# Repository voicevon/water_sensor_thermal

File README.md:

# water_sensor_thermal

污水处理厂三通道脉冲热式管道有液检测传感器（全栈项目：系统设计文档 + KiCad 原理图/PCB + 机械探头工艺 + ESP32 PlatformIO 固件 + 1Hz 串口采数分析工具）。

面向 **碳源、次氯酸钠、聚合氯化铁** 三路强腐蚀/易挂壁/易结垢化工药剂管道（DN75 PPR 水平管），采用 **1 拖 3 单主控盒** 与 **脉冲加热 + 冷却衰减比算法** 实现免标定开箱即用、宽温（-10℃ ~ +60℃）可靠有液/空管检测，支持 **不锈钢/陶瓷探头混合封装**，并通过 **BLE 广播、WiFi Web 后台及 MQTT** 与上位系统（`water_relay` / 监控平台）无缝对接。

---

## 目录结构

```text
water_sensor_thermal/
├── README.md                          # 项目总览与文档索引
├── platformio.ini                     # PlatformIO 构建配置（ESP32 Arduino）
├── src/                               # ESP32 固件源码
│   ├── config.h                       # 硬件引脚、不锈钢/陶瓷算法参数、WiFi/MQTT/BLE 配置
│   ├── main.cpp                       # 1Hz 统一采样、动态分时轮巡调度、串口采数与阶跃测试
│   ├── ThermalChannel.{h,cpp}         # 单通道峰值追踪、冷却衰减比计算、混合封装与迟滞判定
│   ├── ble_adv.{h,cpp}                # 13B BLE 广播封装（兼容 water_sensor_hx711 / water_relay）
│   ├── wifi_mqtt.{h,cpp}              # WiFi 指数退避重连与 MQTT 异步连接/上报/远程控制
│   ├── web_config.{h,cpp}             # AP_STA 配网、Web REST API 与每通道在线配置
│   ├── index_html.h                   # 内嵌紧凑型暗色 SPA 监控与配置页面
│   ├── nvs_config.{h,cpp}             # NVS 掉电持久化（网络、封装类型、阈值、调参基准）
│   └── data_cache.{h,cpp}             # 实时采样数据缓存
├── tools/
│   └── thermal_logger.py              # 1Hz 串口 CSV 采数、阶跃测试与自动绘图分析脚本
├── docs/                              # 完整设计与演进文档
│   ├── design_spec.md                 # 系统设计规格书 (v2.0)：工况、冷却衰减比算法、通信协议
│   ├── main_board_schematic.md        # 主控板原理图与 BOM（最新 DevKit V1 载板版 v4）
│   ├── probe_mechanical_spec.md       # 探头机械结构、标准件清单、混合封装与灌封工艺 (v2.1)
│   ├── hardware_design.md             # 早期裸模组硬件方案草稿与 BOM (v2.0 历史存档)
│   └── pcb_layout.md                  # 早期 PCB 布局规划与布线规范 (v1.0 历史存档)
└── hardware/
    └── pcb/
        ├── main_board_pcb/            # 主控载板 KiCad 工程 (88×78 mm) + Python 生成脚本
        │   ├── main_board_pcb.kicad_pro
        │   ├── main_board_pcb.kicad_sch
        │   ├── main_board_pcb.kicad_pcb
        │   ├── generate_main_sch.py
        │   └── generate_main_pcb.py
        └── probe_mini_pcb/            # 探头微型传感板 KiCad 工程 (4.8×12 mm) + Python 生成脚本
            ├── probe_mini_pcb.kicad_pcb
            └── generate_probe_pcb.py
```

---

## 设计演进与核心特性

1. **算法升级：从温升 $\Delta T$ 演进为免标定冷却衰减比（[design_spec.md](docs/design_spec.md)）**：
   - 统一 1Hz 非阻塞采集 3 路 **SOT-23-3 18B20**（独立 GPIO：`25/26/27`），加热断电后追踪 5 s 真实温度峰值，以归一化冷却衰减比判定有液/空管，天然免疫环境/水温变化、5V 电源压降、阻值公差与连续轮巡热累积漂移。
   - **混合探头自适应**：每通道可在 Web 页面独立切换封装类型并掉电保存（出厂默认 CH1/CH2 不锈钢、CH3 陶瓷）：
     - **0.5 mm 不锈钢管（`PROBE_STEEL`）**：10 s 加热，`frac_10_30 = (T_peak - T10) / (T_peak - T30)`（空气 36~42% vs 水中 58~63%，默认阈值 `>52%` 有液 / `<46%` 空管；3 路全不锈钢总周期 **45 s**）。
     - **2.0 mm 99 刚玉陶瓷管（`PROBE_CERAMIC`）**：30 s 加热，跳过前 10 s 厚壁自身吸热取 `tail(10→30/60s) = (T10 - T30) / (T10 - T60)`（空气 ~66% vs 水中 ~82%，默认阈值 `>75%` 有液 / `<70%` 空管；混合配置自动动态扩展轮巡周期至 **~98 s**）。
2. **主控板演进（[hardware_design.md](docs/hardware_design.md) → [main_board_schematic.md](docs/main_board_schematic.md)）**：
   - 最终量产载板（`v4`，`88×78 mm`）采用插接式 **30-Pin ESP32 DevKit V1 载板**，复用开发板自带 USB 烧录口、3.3V LDO 与 PCB 天线。
   - 宽压 `XL1509-5.0E1`（12V~24V → 恒定 5.0V）+ `GPIO34` 5V 母线电压监测 + 3 路高边 P-MOS 开关（`S8050 + AO3401A`），实现探头 **4 芯共地线缆**（`5V_HEAT / 3V3 / DQ / GND`）及上电/复位/看门狗默认关断防干烧保护。
3. **探头机械结构演进（[probe_mechanical_spec.md](docs/probe_mechanical_spec.md)）**：
   - 强腐蚀工位采用 **100 mm 长 99 刚玉陶瓷盲管（OD10×ID6×壁厚2mm）一管通到底 + 外购 PP/PTFE 10mm 卡套密封接头**，实现零机加工、浸液区零接缝；非强腐/台架工位兼容 0.5 mm 不锈钢盲管。
   - 配套 `4.8 × 12.0 mm` 探头微型 PCB（双 33Ω 1206 并联 = `16.5 Ω`，~1.52 W @ 5V）。
4. **全栈通信与调试工具链**：
   - **BLE 广播**：1Hz 被动广播 `FengBLE`（13 字节载荷），与 `water_sensor_hx711` / `water_relay` 100% 协议兼容。
   - **Web 本地后台**：常驻 `AP_THERMAL`（密码 `12344321`）+ STA 双模，手机/电脑直连 `192.168.4.1` 查看三通道实时对比表、切换探头封装、微调阈值或一键空管自动调参。
   - **MQTT 远程对接**：支持状态上报（`water/sensor/status`）与远程重启/标定（`water/{name}/control`）。
   - **串口采数与阶跃分析**：通过 `tools/thermal_logger.py` 一键记录 1Hz 温度与 5V 压降 CSV 并自动出图。

---

## 文档与工程快速索引

| 文档 / 工程 | 说明 | 状态 |
| :--- | :--- | :--- |
| [docs/design_spec.md](docs/design_spec.md) | 应用工况、冷却衰减比算法、动态时序、BLE/Web/MQTT 通信协议 | **最新系统规格 (v2.0)** |
| [docs/main_board_schematic.md](docs/main_board_schematic.md) | 主控载板完整原理图、引脚表、31 条网络表、BOM 与上电测试指南 | **最新硬件基准 (v4)** |
| [docs/probe_mechanical_spec.md](docs/probe_mechanical_spec.md) | 99 刚玉盲管/不锈钢混合探头结构、标准件清单、灌封 SOP 与验收指标 | **最新结构基准 (v2.1)** |
| [tools/thermal_logger.py](tools/thermal_logger.py) | 1Hz 串口 CSV 采集、单通道阶跃测试与温度曲线自动对比工具 | **最新测试工具** |
| [hardware/pcb/main_board_pcb/](hardware/pcb/main_board_pcb/) | 主控载板 KiCad 原理图/PCB 与 Python 生成脚本 | **最新 PCB** |
| [hardware/pcb/probe_mini_pcb/](hardware/pcb/probe_mini_pcb/) | 探头微型板 KiCad PCB 与 Python 生成脚本 | **最新 PCB** |
| [docs/hardware_design.md](docs/hardware_design.md) | 早期裸模组方案详细电路与 BOM | 历史设计存档 |
| [docs/pcb_layout.md](docs/pcb_layout.md) | 早期 PCB 正反面布局规范与反热短路过孔设计要点 | 历史设计存档 |

---

## 固件编译、烧录与台架采数

本项目使用 [PlatformIO](https://platformio.org/) 构建（目标板：`esp32dev`）：

```bash
# 编译固件
pio run

# 烧录到 ESP32 DevKit V1
pio run -t upload

# 打开串口监视器（115200 bps）
pio device monitor
```

使用 Python 脚本进行 1Hz 串口采数与自动绘图（依赖 `pyserial`、`matplotlib`）：

```bash
# 自动检测串口，采集 15 分钟并自动生成对比图（保存至 logs/）
python tools/thermal_logger.py --duration 15

# 对指定通道执行阶跃测试（如 CH3 加热 60s + 冷却 180s）
python tools/thermal_logger.py --duration 5 --step "step 3 60 180"

# 对已有 CSV 重新统计并出图
python tools/thermal_logger.py --plot-only logs/thermal_20261128_150855.csv
```

> ⚠️ **上电安全提醒**：切勿同时接入载板 `J1` 的 12~24V 工业电源与电脑 USB 调试线，烧录时请拔下 DevKit 单独连 USB 或断开 `J1` 电源。详见 [main_board_schematic.md 第 7 节](docs/main_board_schematic.md#7-焊接装配与首次上电测试指南)。

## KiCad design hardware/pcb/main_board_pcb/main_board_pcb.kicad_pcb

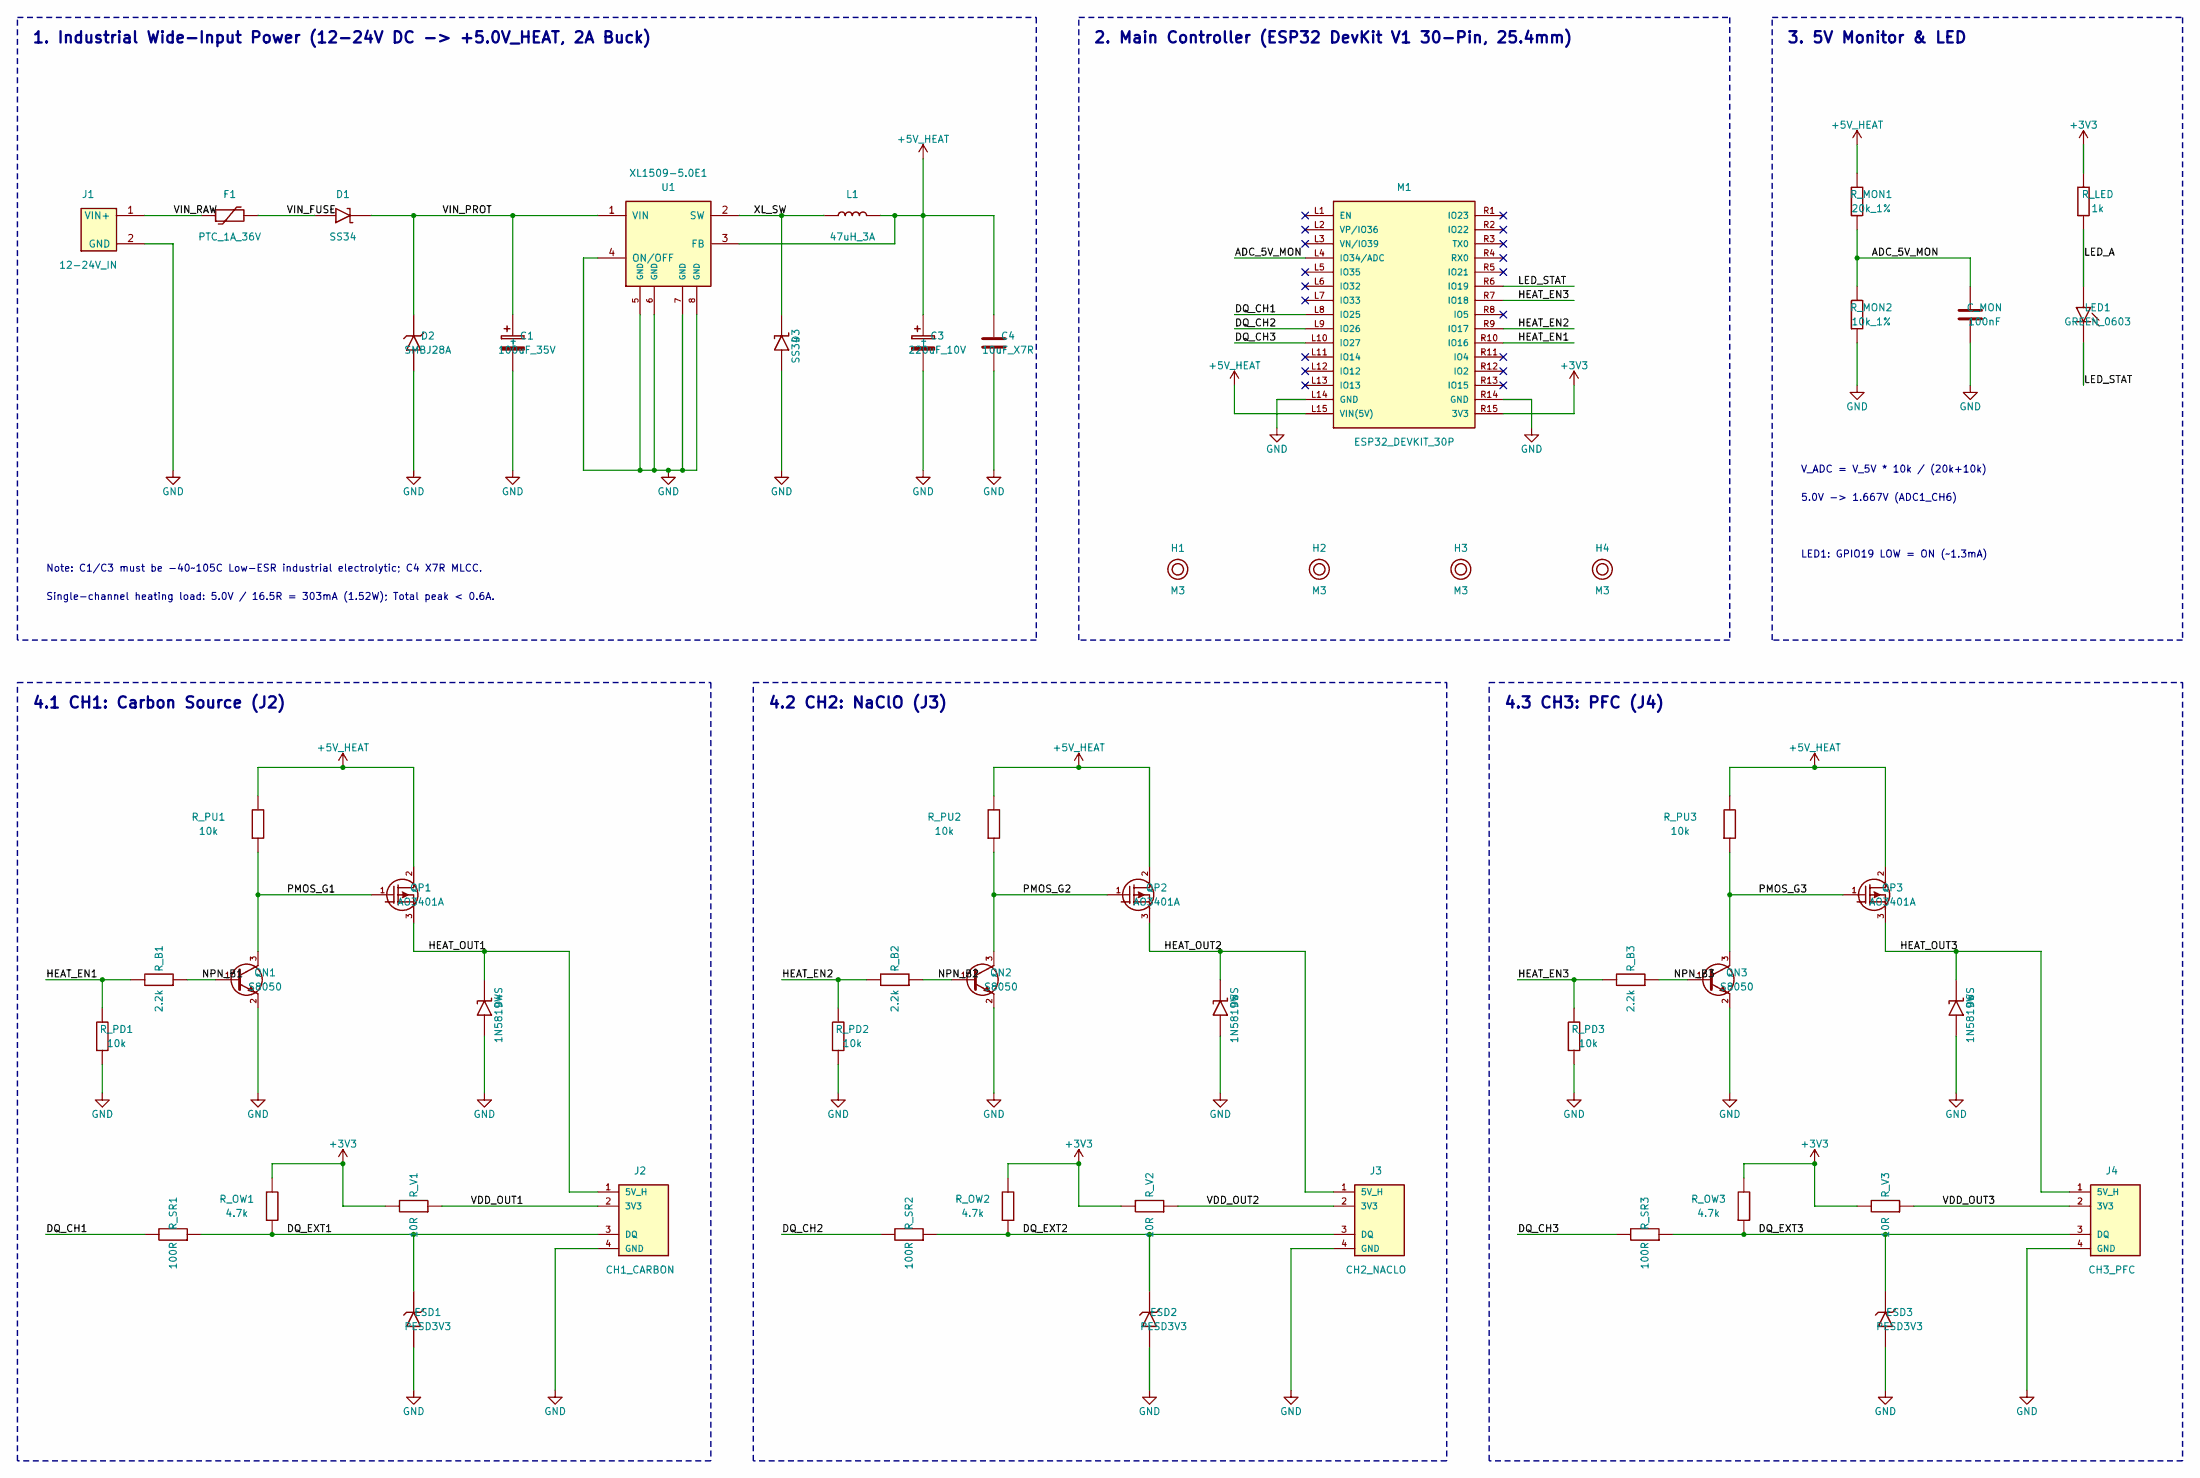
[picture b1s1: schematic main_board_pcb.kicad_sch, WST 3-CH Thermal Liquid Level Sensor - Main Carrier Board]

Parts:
C1: 100uF_35V; CP_Radial_D8.0mm_P3.50mm
C3: 220uF_10V; CP_Radial_D6.3mm_P2.50mm
C4: 10uF_X7R; C_0805
C_MON: 100nF; C_0603
D1, D3: SS34; D_SMA
D2: SMBJ28A; D_SMB
D4, D5, D6: 1N5819WS; D_SOD-123
ESD1, ESD2, ESD3: PESD3V3; D_SOD-323
F1: PTC_1A_36V; Fuse_1812
H1, H2, H3, H4: M3; MountingHole_3.2mm_M3
J1: 12-24V_IN; KF2EDGK_2P_P5.08mm
J2: CH1_CARBON; KF2EDGK_4P_P3.81mm
J3: CH2_NACLO; KF2EDGK_4P_P3.81mm
J4: CH3_PFC; KF2EDGK_4P_P3.81mm
L1: 47uH_3A; L_10x10
LED1: GREEN_0603; LED_0603
M1: ESP32_DEVKIT_30P; ESP32_DevKit_V1_30Pin_25.4mm
QN1, QN2, QN3: S8050; SOT-23
QP1, QP2, QP3: AO3401A; SOT-23
R_B1, R_B2, R_B3: 2.2k; R_0603
R_LED: 1k; R_0603
R_MON1: 20k_1%; R_0603
R_MON2: 10k_1%; R_0603
R_OW1, R_OW2, R_OW3: 4.7k; R_0603
R_PD1, R_PD2, R_PD3: 10k; R_0603
R_PU1, R_PU2, R_PU3: 10k; R_0603
R_SR1, R_SR2, R_SR3: 100R; R_0603
R_V1, R_V2, R_V3: 10R; R_0603
U1: XL1509-5.0E1; SOIC-8

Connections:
+3V3: M1.R15 (3V3), R_LED.1, R_OW1.1, R_OW2.1, R_OW3.1, R_V1.1, R_V2.1, R_V3.1
+5V_HEAT: C3.1 (+), C4.1, L1.2, M1.L15 (VIN(5V)), QP1.2 (S), QP2.2 (S), QP3.2 (S), R_MON1.1, R_PU1.1, R_PU2.1, R_PU3.1, U1.3 (FB)
ADC_5V_MON: C_MON.1, M1.L4 (IO34/ADC), R_MON1.2, R_MON2.1
DQ_CH1: M1.L8 (IO25), R_SR1.1
DQ_CH2: M1.L9 (IO26), R_SR2.1
DQ_CH3: M1.L10 (IO27), R_SR3.1
DQ_EXT1: ESD1.1 (K), J2.3 (DQ), R_OW1.2, R_SR1.2
DQ_EXT2: ESD2.1 (K), J3.3 (DQ), R_OW2.2, R_SR2.2
DQ_EXT3: ESD3.1 (K), J4.3 (DQ), R_OW3.2, R_SR3.2
GND: C1.2 (-), C3.2 (-), C4.2, C_MON.2, D2.2 (A), D3.1 (A), D4.1 (A), D5.1 (A), D6.1 (A), ESD1.2 (A), ESD2.2 (A), ESD3.2 (A), J1.2 (GND), J2.4 (GND), J3.4 (GND), J4.4 (GND), M1.L14 (GND), M1.R14 (GND), QN1.2 (E), QN2.2 (E), QN3.2 (E), R_MON2.2, R_PD1.2, R_PD2.2, R_PD3.2, U1.4 (ON/OFF), U1.5 (GND), U1.6 (GND), U1.7 (GND), U1.8 (GND)
HEAT_EN1: M1.R10 (IO16), R_B1.1, R_PD1.1
HEAT_EN2: M1.R9 (IO17), R_B2.1, R_PD2.1
HEAT_EN3: M1.R7 (IO18), R_B3.1, R_PD3.1
HEAT_OUT1: D4.2 (K), J2.1 (5V_H), QP1.3 (D)
HEAT_OUT2: D5.2 (K), J3.1 (5V_H), QP2.3 (D)
HEAT_OUT3: D6.2 (K), J4.1 (5V_H), QP3.3 (D)
LED_A: LED1.1 (A), R_LED.2
LED_STAT: LED1.2 (K), M1.R6 (IO19)
NPN_B1: QN1.1 (B), R_B1.2
NPN_B2: QN2.1 (B), R_B2.2
NPN_B3: QN3.1 (B), R_B3.2
PMOS_G1: QN1.3 (C), QP1.1 (G), R_PU1.2
PMOS_G2: QN2.3 (C), QP2.1 (G), R_PU2.2
PMOS_G3: QN3.3 (C), QP3.1 (G), R_PU3.2
VDD_OUT1: J2.2 (3V3), R_V1.2
VDD_OUT2: J3.2 (3V3), R_V2.2
VDD_OUT3: J4.2 (3V3), R_V3.2
VIN_FUSE: D1.1 (A), F1.2
VIN_PROT: C1.1 (+), D1.2 (K), D2.1 (K), U1.1 (VIN)
VIN_RAW: F1.1, J1.1 (VIN+)
XL_SW: D3.2 (K), L1.1, U1.2 (SW)

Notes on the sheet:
1. Industrial Wide-Input Power (12-24V DC -> +5.0V_HEAT, 2A Buck)
Note: C1/C3 must be -40~105C Low-ESR industrial electrolytic; C4 X7R MLCC.
Single-channel heating load: 5.0V / 16.5R = 303mA (1.52W); Total peak < 0.6A.
2. Main Controller (ESP32 DevKit V1 30-Pin, 25.4mm)
3. 5V Monitor & LED
V_ADC = V_5V * 10k / (20k+10k)
5.0V -> 1.667V (ADC1_CH6)
LED1: GPIO19 LOW = ON (~1.3mA)
4.1 CH1: Carbon Source (J2)
4.2 CH2: NaClO (J3)
4.3 CH3: PFC (J4)

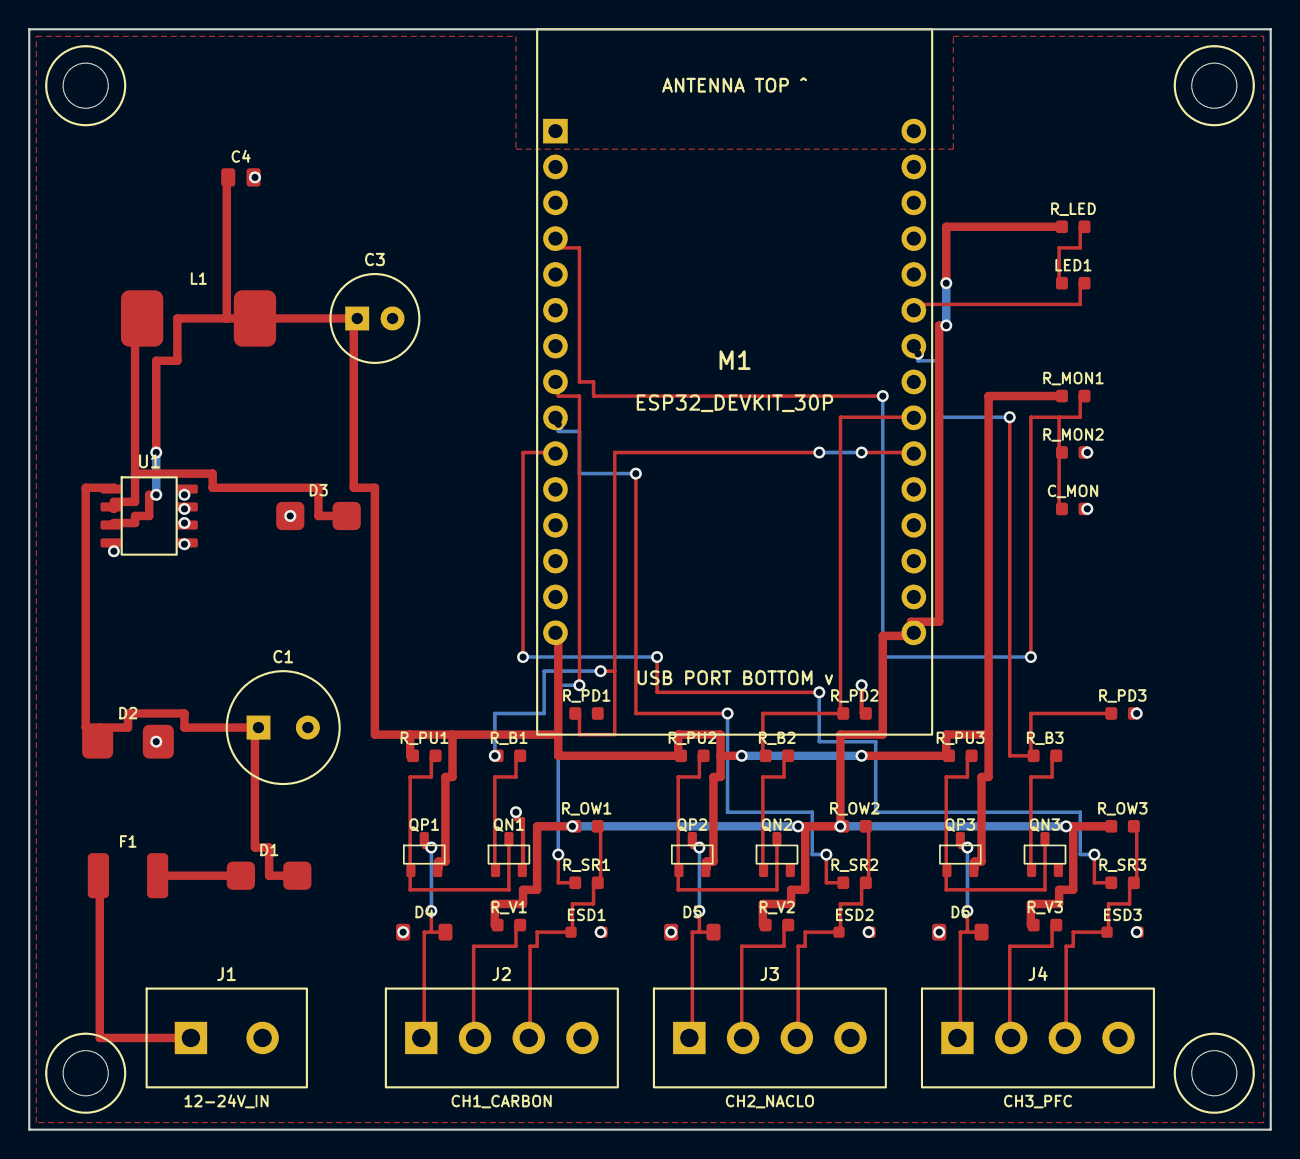
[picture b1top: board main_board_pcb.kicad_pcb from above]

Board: 2 copper layers, 88.0 x 78.0 mm, 53 parts (0 on the bottom side), 31 nets.

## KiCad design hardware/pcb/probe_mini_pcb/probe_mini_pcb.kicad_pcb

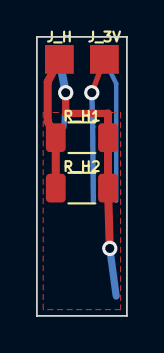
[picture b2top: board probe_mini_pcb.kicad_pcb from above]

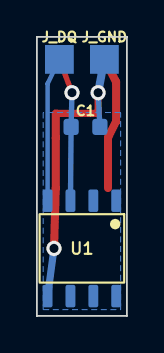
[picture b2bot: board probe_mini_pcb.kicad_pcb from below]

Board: 2 copper layers, 5.0 x 15.5 mm, 8 parts (4 on the bottom side), 4 nets.

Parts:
C1: 100nF; C_0603_1608Metric
J_3V: 3V3; WirePad_1.6x1.6
J_DQ: DQ; WirePad_1.6x1.6
J_GND: GND; WirePad_1.6x1.6
J_H: H+; WirePad_1.6x1.6
R_H1, R_H2: 33R_0.5W; R_1206_3216Metric
U1: DS18B20Z_SOP8; SOIC-8_3.9x4.9mm_P1.27mm

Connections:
DQ: J_DQ.1, U1.4
GND: C1.1, J_GND.1, R_H1.2, R_H2.2, U1.5
HEAT_5V: J_H.1, R_H1.1, R_H2.1
VDD_3V3: C1.2, J_3V.1, U1.3

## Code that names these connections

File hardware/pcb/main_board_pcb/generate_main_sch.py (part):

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    f1 = sb.add_symbol("Custom:Fuse_PTC", "F1", "PTC_1A_36V", "Fuse:Fuse_1812",
                       53.34, 50.80, 0, ref_off=(0, -3.81), val_off=(0, 3.81))
    sb.add_wire(j1["1"], f1["1"])
    sb.add_label("VIN_RAW", (43.18, 50.80))

    # D1: SS34 Reverse Polarity Protection
    d1 = sb.add_symbol("Custom:D_Schottky_AK", "D1", "SS34", "Diode_SMD:D_SMA",
                       73.66, 50.80, 0, ref_off=(0, -3.81), val_off=(0, 3.81))
    sb.add_wire(f1["2"], d1["1"])
    sb.add_label("VIN_FUSE", (63.50, 50.80))

    # VIN_PROT rail to D2, C1, U1.1
    d2 = sb.add_symbol("Custom:D_TVS_KA", "D2", "SMBJ28A", "Diode_SMD:D_SMB",
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                       132.08, 55.88, 0, ref_off=(0, -10.16), val_off=(0, -12.70))

    sb.add_wire(d1["2"], u1["1"])
    sb.add_label("VIN_PROT", (91.44, 50.80))
    sb.add_wire((86.36, 50.80), d2["1"])
    sb.add_junction((86.36, 50.80))
    sb.add_wire(d2["2"], (86.36, 96.52))
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    sb.add_power("GND", 132.08, 96.52)
    sb.add_junction((132.08, 96.52))

    # D3: SS34 Freewheeling Diode (Anode=1=GND, Cathode=2=XL_SW -> rot=90 puts Pin1 bottom, Pin2 top? Let's check!)
    # Custom:D_Schottky_AK has Pin1=(-5.08, 0), Pin2=(+5.08, 0).
    # With rot=90: Pin1 -> (sx, sy + 5.08) [BOTTOM], Pin2 -> (sx, sy - 5.08) [TOP]!
    d3 = sb.add_symbol("Custom:D_Schottky_AK", "D3", "SS34", "Diode_SMD:D_SMA",
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                       165.10, 50.80, 0, ref_off=(0, -3.81), val_off=(0, 3.81))

    sb.add_wire(u1["2"], l1["1"])
    sb.add_label("XL_SW", (147.32, 50.80))
    sb.add_wire((152.40, 50.80), d3["2"])
    sb.add_junction((152.40, 50.80))
    sb.add_wire(d3["1"], (152.40, 96.52))
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
    # Left side connections
    left_used = {
        "L4": ("ADC_5V_MON", "label"),
        "L8": ("DQ_CH1", "label"),
        "L9": ("DQ_CH2", "label"),
        "L10": ("DQ_CH3", "label"),
        "L14": ("GND", "power"),
        "L15": ("+5V_HEAT", "power"),
    }
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
    # Right side connections
    right_used = {
        "R6": ("LED_STAT", "label"),
        "R7": ("HEAT_EN3", "label"),
        "R9": ("HEAT_EN2", "label"),
        "R10": ("HEAT_EN1", "label"),
        "R14": ("GND", "power"),
        "R15": ("+3V3", "power"),
    }
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    sb.add_wire(rm1["2"], rm2["1"])
    sb.add_poly_wire([(345.44, 58.42), (365.76, 58.42), cm["1"]])
    sb.add_junction((345.44, 58.42))
    sb.add_label("ADC_5V_MON", (347.98, 58.42))
    sb.add_wire(rm2["2"], (345.44, 81.28))
    sb.add_power("GND", 345.44, 81.28)
    sb.add_wire(cm["2"], (365.76, 81.28))
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    sb.add_wire(rled["1"], (386.08, 38.10))
    sb.add_power("+3V3", 386.08, 38.10)
    sb.add_wire(rled["2"], led1["1"])
    sb.add_label("LED_A", (386.08, 58.42))
    sb.add_wire(led1["2"], (386.08, 81.28))
    sb.add_label("LED_STAT", (386.08, 81.28))

    sb.add_note(335.28, 96.52, "V_ADC = V_5V * 10k / (20k+10k)")
    sb.add_note(335.28, 101.60, "5.0V -> 1.667V (ADC1_CH6)")
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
